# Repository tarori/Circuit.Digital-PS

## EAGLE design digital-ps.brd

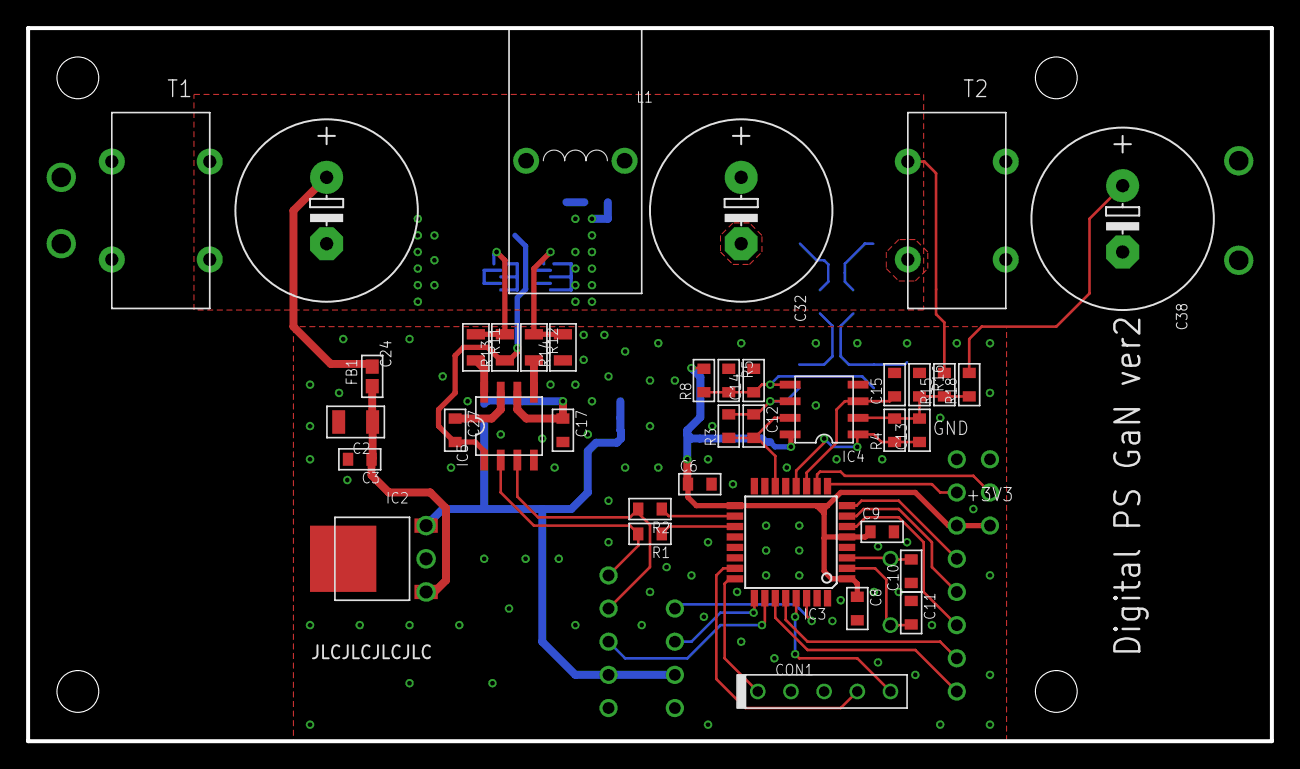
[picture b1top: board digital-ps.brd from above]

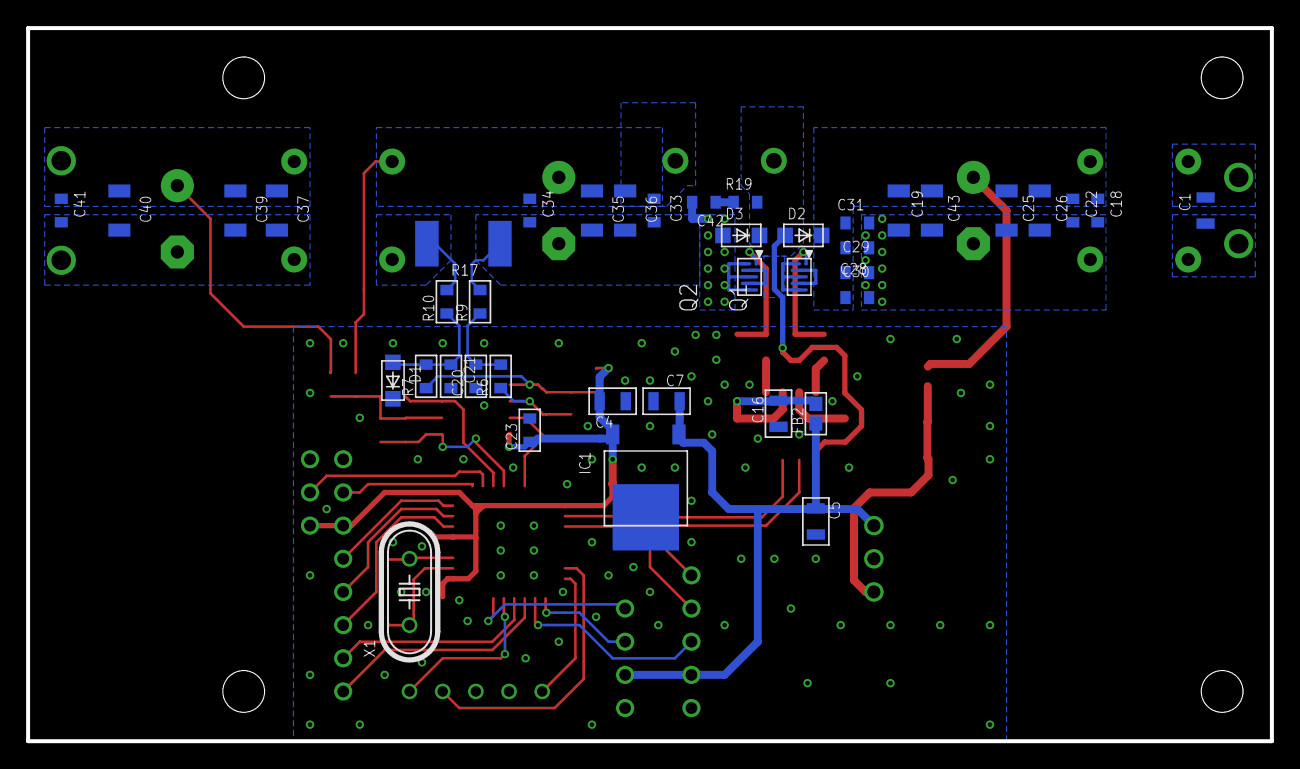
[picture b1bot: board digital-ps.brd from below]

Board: 4 copper layers, 95.2 x 54.6 mm, 107 parts (41 on the bottom side), 46 nets.

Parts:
C1: 1u; 2012-2
C2: 10u; 3216
C3, C6, C8, C9, C17, C23, C27: 0.1u; 1608
C4, C5, C7, C16: 10u; 2012
C10, C11: 10p; 1608
C12, C13, C14, C15, C20, C21: 1000p; 1608
C18, C22, C28, C29, C30, C31, C33, C34, C41: 1u; 1608-2
C19, C25, C26, C35, C36, C37, C39, C40, C43: 10u; 3225-2
C24: 1000u; E5-13
C32: DNP; E5-13
C38: 470u; E5-13
C42: 470; 1608-2
CON1: SWD_CON
D1: 1N4148; SOD123
D2, D3: SBD-1A2; SOD123
DR1, DR2, DR3, DR4: HOLE-3.2; HOLE_3.2
FB1: FB-1608FB; 1608-FB
FB2: FB; 1608-J
IC1: 3.3V; P-HSIP3_2.30A
IC2: 7805; TO220-SOP-DUAL
IC3: STM32F334K8; TQFP32-08
IC4: OPA; SOP8
IC5: MCP14700; SOP8
L1: 47u; L7-10
Q1, Q2: EPC2052; EPC2055
R1, R2: 120; 1608
R3, R4, R5, R15: 10k; 1608
R6, R7, R16: 1k; 1608
R8: 1M; 1608
R9, R10: 39; 1608
R11, R12: 10; 2012
R13, R14: 10k; 2012
R17: 10m; 6432
R18: DNP; 1608
R19: 2; 1608-2
T1, T2: COMMON_FILTER-SMALL; COMMON_FILTER__SMALL
TP1: PA0; TESTPIN
TP2: PA1; TESTPIN
TP3: PA2; TESTPIN
TP4: PA3; TESTPIN
TP5: IN+; TESTPIN-BIG
TP6: IN-; TESTPIN-BIG
TP7: OUT+; TESTPIN-BIG
TP8: OUT-; TESTPIN-BIG
TP9: PA4; TESTPIN
TP10: PB7; TESTPIN
TP11: PB5; TESTPIN
TP15, TP24: +3V3; TESTPIN
TP16, TP26: +5V; TESTPIN
TP17, TP18, TP25, TP27: GND; TESTPIN
TP19: PWML; TESTPIN
TP20: PWMH; TESTPIN
TP21: PA15; TESTPIN
TP22: PB3; TESTPIN
TP23: PB4; TESTPIN
X1: 12MHz; HC49/S

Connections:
+3V3: C4.1, C6.1, C8.1, C9.1, C23.1, IC1.3, IC3.1, IC3.5, IC3.17, IC4.8, R8.2, TP15.1, TP24.1
+5V: C5.1, C7.1, FB2.1, IC1.1, IC2.3, IC2.6, TP16.1, TP26.1
+5VP: C16.1, C17.1, FB2.2, IC5.6
GND: C2.2, C3.2, C4.2, C5.2, C6.2, C7.2, C8.2, C9.2, C10.1, C11.1, C14.2, C15.2, C16.2, C17.2, C18.2, C19.2, C20.1, C21.2, C22.2, C23.2, C24.-, C25.2, C26.2, C28.2, C29.2, C30.2, C31.2, C32.-, C33.2, C34.2, C35.2, C36.2, C42.2, C43.2, CON1.3, D1.2, D3.1, IC1.2, IC2.2, IC2.5, IC3.16, IC3.31, IC3.32, IC4.4, IC5.4, Q2.2, Q2.4, Q2.6, R5.1, R9.2, R14.1, R16.1, R17.1, T1.2, TP17.1, TP18.1, TP25.1, TP27.1
IN+: C1.1, T1.4, TP5.1
IN-: C1.2, T1.1, TP6.1
ISENSE: R10.2, R17.2, T2.1
unnamed: IC3.18, R2.1
unnamed: IC3.19, R1.1
unnamed: C12.2, IC3.14, IC4.7, R3.1
unnamed: C2.1, C3.1, FB1.2, IC2.1, IC2.4
unnamed: C14.1, IC4.5, R5.2, R7.1, R8.1
unnamed: IC5.8, R11.2
unnamed: C27.1, IC5.7
unnamed: C20.2, R6.2, R9.1
unnamed: C42.1, R19.1
unnamed: C21.1, D1.1, R7.2, R10.1
unnamed: IC5.5, R12.2
unnamed: IC3.9, TP4.1
unnamed: IC3.10, TP9.1
unnamed: IC3.6, TP1.1
unnamed: IC3.7, TP2.1
unnamed: IC3.8, TP3.1
unnamed: IC3.30, TP10.1
unnamed: IC3.28, TP11.1
unnamed: IC3.27, TP23.1
unnamed: C11.2, IC3.2, X1.1
unnamed: C10.2, IC3.3, X1.2
unnamed: IC3.26, TP22.1
unnamed: IC3.25, TP21.1
unnamed: C12.1, IC4.6, R3.2, R6.1
unnamed: C13.1, IC3.12, IC4.1, R4.1
unnamed: C15.1, IC3.11, IC4.3
unnamed: Q1.1, R11.1, R13.2
unnamed: Q2.1, R12.1, R14.2
OUT: C32.+, C33.1, C34.1, C35.1, C36.1, L1.2, R15.2, T2.4
OUT+: C37.1, C38.+, C39.1, C40.1, C41.1, R18.2, T2.3, TP7.1
OUT-: C37.2, C38.-, C39.2, C40.2, C41.2, T2.2, TP8.1
PWMH: IC5.2, R1.2, TP20.1
PWML: IC5.3, R2.2, TP19.1
SW: C27.2, D2.1, D3.2, IC5.1, L1.1, Q1.2, Q1.4, Q1.6, Q2.3, Q2.5, R13.1, R19.2
SWCLK: CON1.1, IC3.24
SWDIO: CON1.4, IC3.23
UART_TX: CON1.5, IC3.29
VFB: C13.2, IC4.2, R4.2, R15.1, R16.2, R18.1
VP: C18.1, C19.1, C22.1, C24.+, C25.1, C26.1, C28.1, C29.1, C30.1, C31.1, C43.1, D2.2, FB1.1, Q1.3, Q1.5, T1.3

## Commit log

2022-09-11 FETのゲート逆だった
2022-09-11 GaN FET
2022-09-11 F303 GaN FET
